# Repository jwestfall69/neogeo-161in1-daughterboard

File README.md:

# neogeo-161in1-daughterboard

## Overview
Vortex's [VTXCart](https://github.com/xvortex/VTXCart/tree/main) project allows rewriting the flash/CPLD chips on the 161in1 V3 cart to contain whatever neogeo games you want.  Part of this process involves removing small daughterboards that contain the C/V roms.  These daughterboards are very thin and use a surface mounted 1.27 DIP connector.  It only takes a small amount of pull force on the board to cause the 1.27mm DIP pads to be pulled off the board.

This neogeo-161in1-daughterboard project is a replacement daughterboard that uses a through hole version of the 1.27mm DIP connector.

**Bare Boards:**<br>

**Assembled Top/Bottom:**<br>

## Manufacturing
You should select board thickness of 0.8mm.

The board has very fine pitched (0.8mm) castellated holes on it.  Ideally you would want to pick the castellated holes option with the PCB manufacture so they get cut cleanly.  However the PCB manufacturer will likely reject the order if you pick the option because most require 0.6mm hole diameter and 0.6mm distance between castellated holes.

Placing the order without the castellated holes option should go through but will cause the holes to be slightly mangled and look something like this.

You can see how the copper from the left side of the through hole is still there just kinda push flat against the cut path.  To fix this you can use fine tipped tweezers to push that extra copper into the right side of the hole.  It should end up looking something like this, which is good enough.

Don't attempt to pull the extra copper off or you could rip out all of the copper from the through hole.

Once done, I would suggest using a magnifying glass to verify you see raw pcb between each of the castellated holes.

## Parts
The F0095H0 flash chip comes from your damaged daughterboard.

The dip male connectors are dual row 1.27mm, 22 pins per row, 44 pins total per connector.  Best bet is to just by some cheap 2x50 pin connectors and cut them down to size.

## Soldering
I'm going to assume you don't really need soldering advice if you are taking on the task of making a VTXCart.  But I will warn you to be careful when soldering the dip connector.  It doesn't seem to take much heat and side pressure to cause the individual pins to shift around and you can end up with pins pointing all over the place instead of 2 straight lines.

## Install

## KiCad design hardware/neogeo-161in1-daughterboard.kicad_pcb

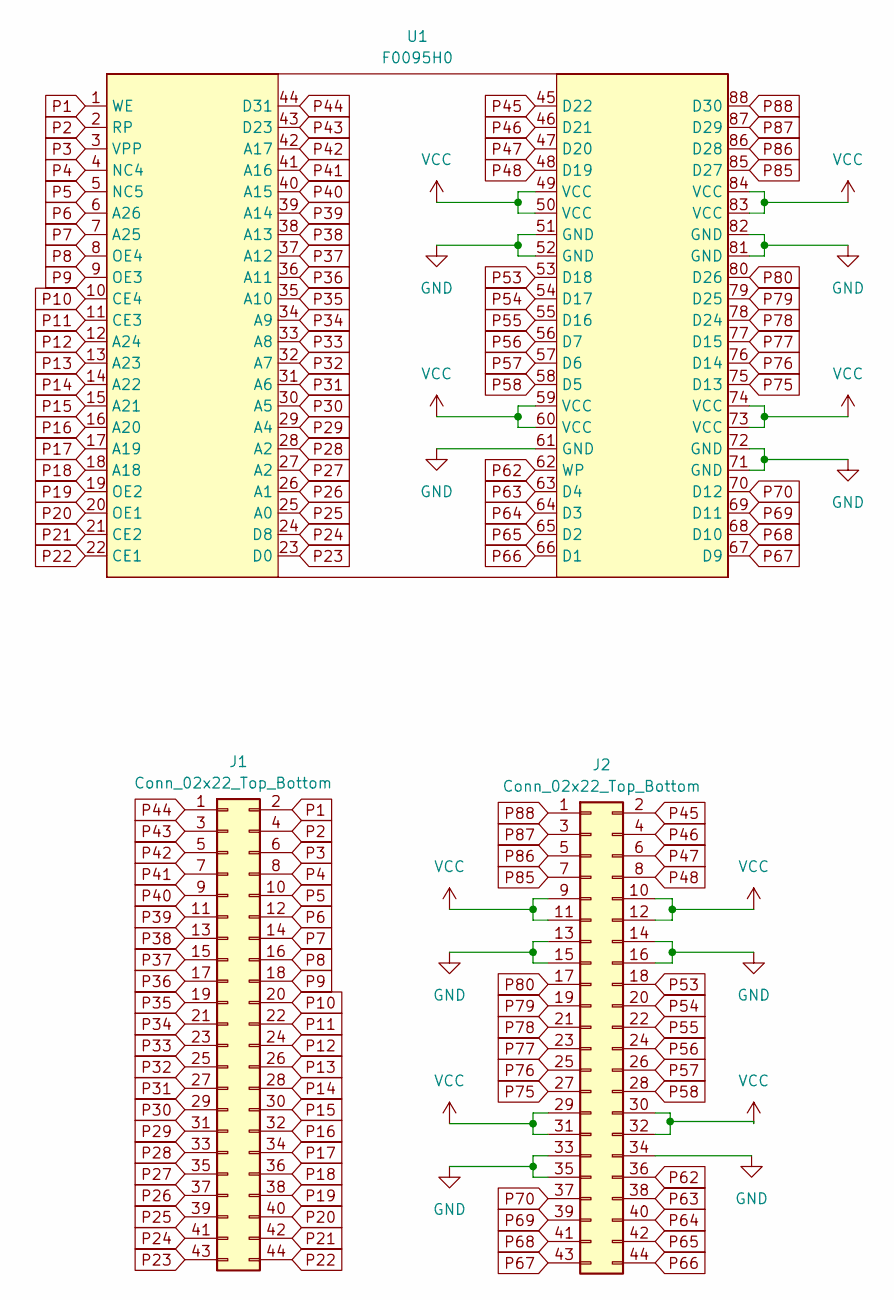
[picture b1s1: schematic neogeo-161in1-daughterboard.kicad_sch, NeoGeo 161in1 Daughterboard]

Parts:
J1, J2: Conn_02x22_Top_Bottom; PinHeader_2x22_P1.27mm_Vertical
U1: F0095H0

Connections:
GND: J2.13, J2.14, J2.15, J2.16, J2.33, J2.34, J2.35, U1.51 (GND), U1.52 (GND), U1.61 (GND), U1.71 (GND), U1.72 (GND), U1.81 (GND), U1.82 (GND)
P1: J1.2, U1.1 (WE)
P2: J1.4, U1.2 (RP)
P3: J1.6, U1.3 (VPP)
P4: J1.8, U1.4 (NC4)
P5: J1.10, U1.5 (NC5)
P6: J1.12, U1.6 (A26)
P7: J1.14, U1.7 (A25)
P8: J1.16, U1.8 (OE4)
P9: J1.18, U1.9 (OE3)
P10: J1.20, U1.10 (CE4)
P11: J1.22, U1.11 (CE3)
P12: J1.24, U1.12 (A24)
P13: J1.26, U1.13 (A23)
P14: J1.28, U1.14 (A22)
P15: J1.30, U1.15 (A21)
P16: J1.32, U1.16 (A20)
P17: J1.34, U1.17 (A19)
P18: J1.36, U1.18 (A18)
P19: J1.38, U1.19 (OE2)
P20: J1.40, U1.20 (OE1)
P21: J1.42, U1.21 (CE2)
P22: J1.44, U1.22 (CE1)
P23: J1.43, U1.23 (D0)
P24: J1.41, U1.24 (D8)
P25: J1.39, U1.25 (A0)
P26: J1.37, U1.26 (A1)
P27: J1.35, U1.27 (A2)
P28: J1.33, U1.28 (A2)
P29: J1.31, U1.29 (A4)
P30: J1.29, U1.30 (A5)
P31: J1.27, U1.31 (A6)
P32: J1.25, U1.32 (A7)
P33: J1.23, U1.33 (A8)
P34: J1.21, U1.34 (A9)
P35: J1.19, U1.35 (A10)
P36: J1.17, U1.36 (A11)
P37: J1.15, U1.37 (A12)
P38: J1.13, U1.38 (A13)
P39: J1.11, U1.39 (A14)
P40: J1.9, U1.40 (A15)
P41: J1.7, U1.41 (A16)
P42: J1.5, U1.42 (A17)
P43: J1.3, U1.43 (D23)
P44: J1.1, U1.44 (D31)
P45: J2.2, U1.45 (D22)
P46: J2.4, U1.46 (D21)
P47: J2.6, U1.47 (D20)
P48: J2.8, U1.48 (D19)
P53: J2.18, U1.53 (D18)
P54: J2.20, U1.54 (D17)
P55: J2.22, U1.55 (D16)
P56: J2.24, U1.56 (D7)
P57: J2.26, U1.57 (D6)
P58: J2.28, U1.58 (D5)
P62: J2.36, U1.62 (WP)
P63: J2.38, U1.63 (D4)
P64: J2.40, U1.64 (D3)
P65: J2.42, U1.65 (D2)
P66: J2.44, U1.66 (D1)
P67: J2.43, U1.67 (D9)
P68: J2.41, U1.68 (D10)
P69: J2.39, U1.69 (D11)
P70: J2.37, U1.70 (D12)
P75: J2.27, U1.75 (D13)
P76: J2.25, U1.76 (D14)
P77: J2.23, U1.77 (D15)
P78: J2.21, U1.78 (D24)
P79: J2.19, U1.79 (D25)
P80: J2.17, U1.80 (D26)
P85: J2.7, U1.85 (D27)
P86: J2.5, U1.86 (D28)
P87: J2.3, U1.87 (D29)
P88: J2.1, U1.88 (D30)
VCC: J2.9, J2.10, J2.11, J2.12, J2.29, J2.30, J2.31, J2.32, U1.49 (VCC), U1.50 (VCC), U1.59 (VCC), U1.60 (VCC), U1.73 (VCC), U1.74 (VCC), U1.83 (VCC), U1.84 (VCC)

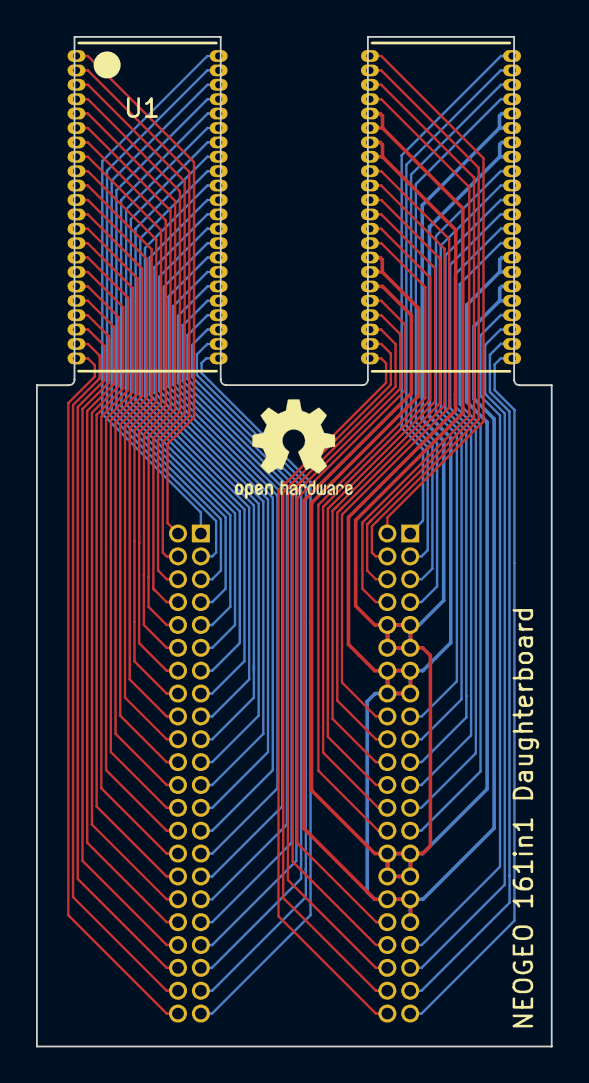
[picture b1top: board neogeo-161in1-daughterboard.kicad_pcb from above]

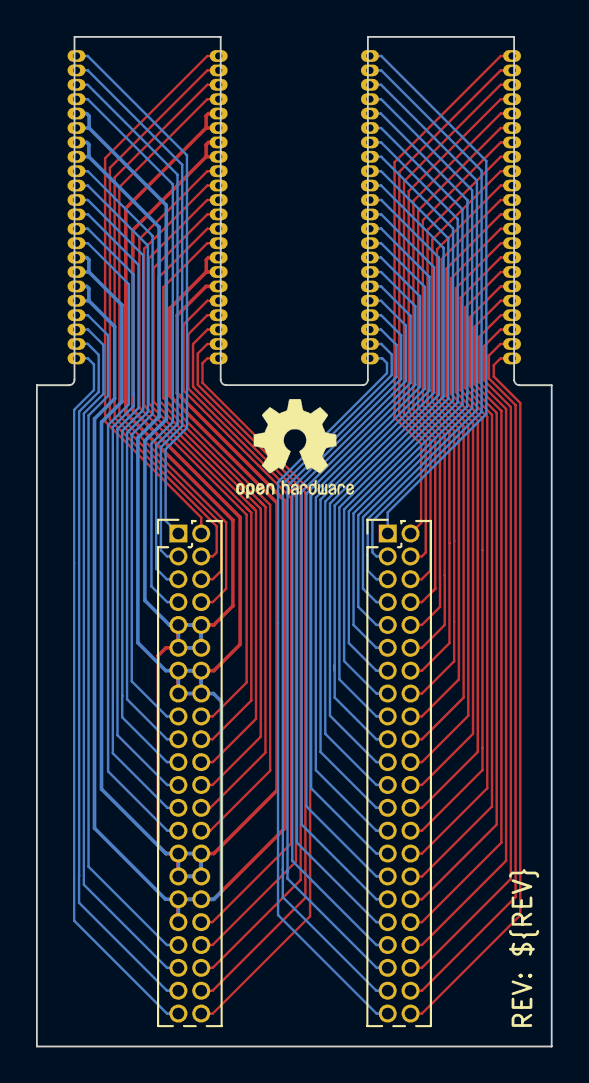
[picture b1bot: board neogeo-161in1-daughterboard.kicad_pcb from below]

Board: 2 copper layers, 28.6 x 56.1 mm, 3 parts (2 on the bottom side), 75 nets.

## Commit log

2023-10-07 Initial checkin
2023-10-18 Add images to docs
2023-10-19 Add installed picture
